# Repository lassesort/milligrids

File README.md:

# Milligrids
11hp version of Grids (topographic drum sequencer eurorack module) by Mutable Instruments

# NOTICE
IF YOU BUILD THIS DO NOT BOTHER OLIVIER GILLET, MUTABLE INSTRUMENTS or THE MUTABLE INSTRUMENTS FORUM WITH QUESTIONS! JUST DON'T! 

I might help you. But my priorities are in this order: my kids, my spouse, my job, my jobby, my mental health, looking out of the window, finishing my pile of synth related pcbs, watching videos on Youtube about country borders, manufacturing processes and cyclists from the 80s and 90s, and finally, somewhere close to the end of this list: helping you when you're failing at programming a Milligrids or needing help finding alternatives for parts in the BOM. ;)

# License
Code (AVR projects): GPL3.0.

Hardware: cc-by-sa-3.0

Grids: https://mutable-instruments.net/modules/grids/

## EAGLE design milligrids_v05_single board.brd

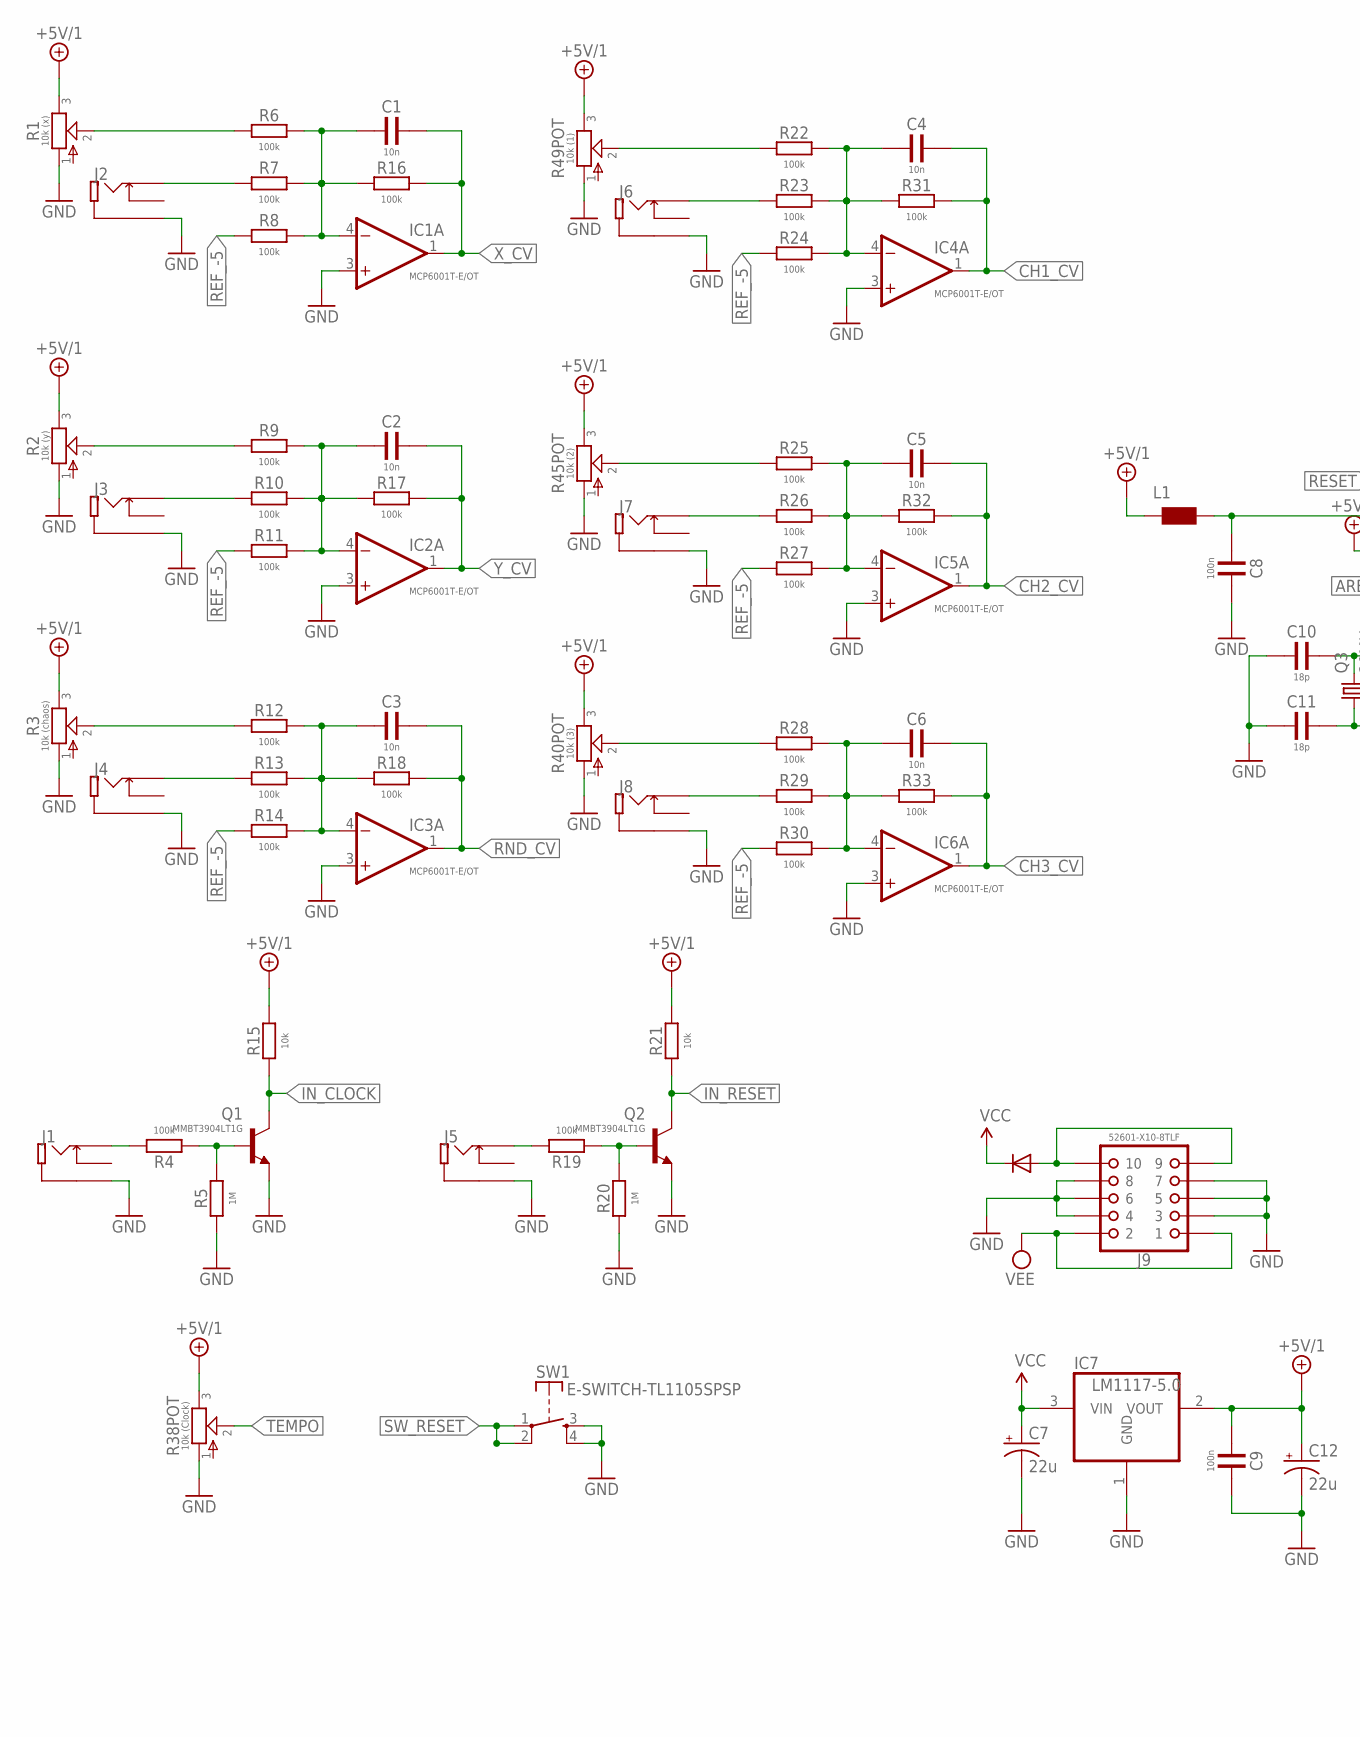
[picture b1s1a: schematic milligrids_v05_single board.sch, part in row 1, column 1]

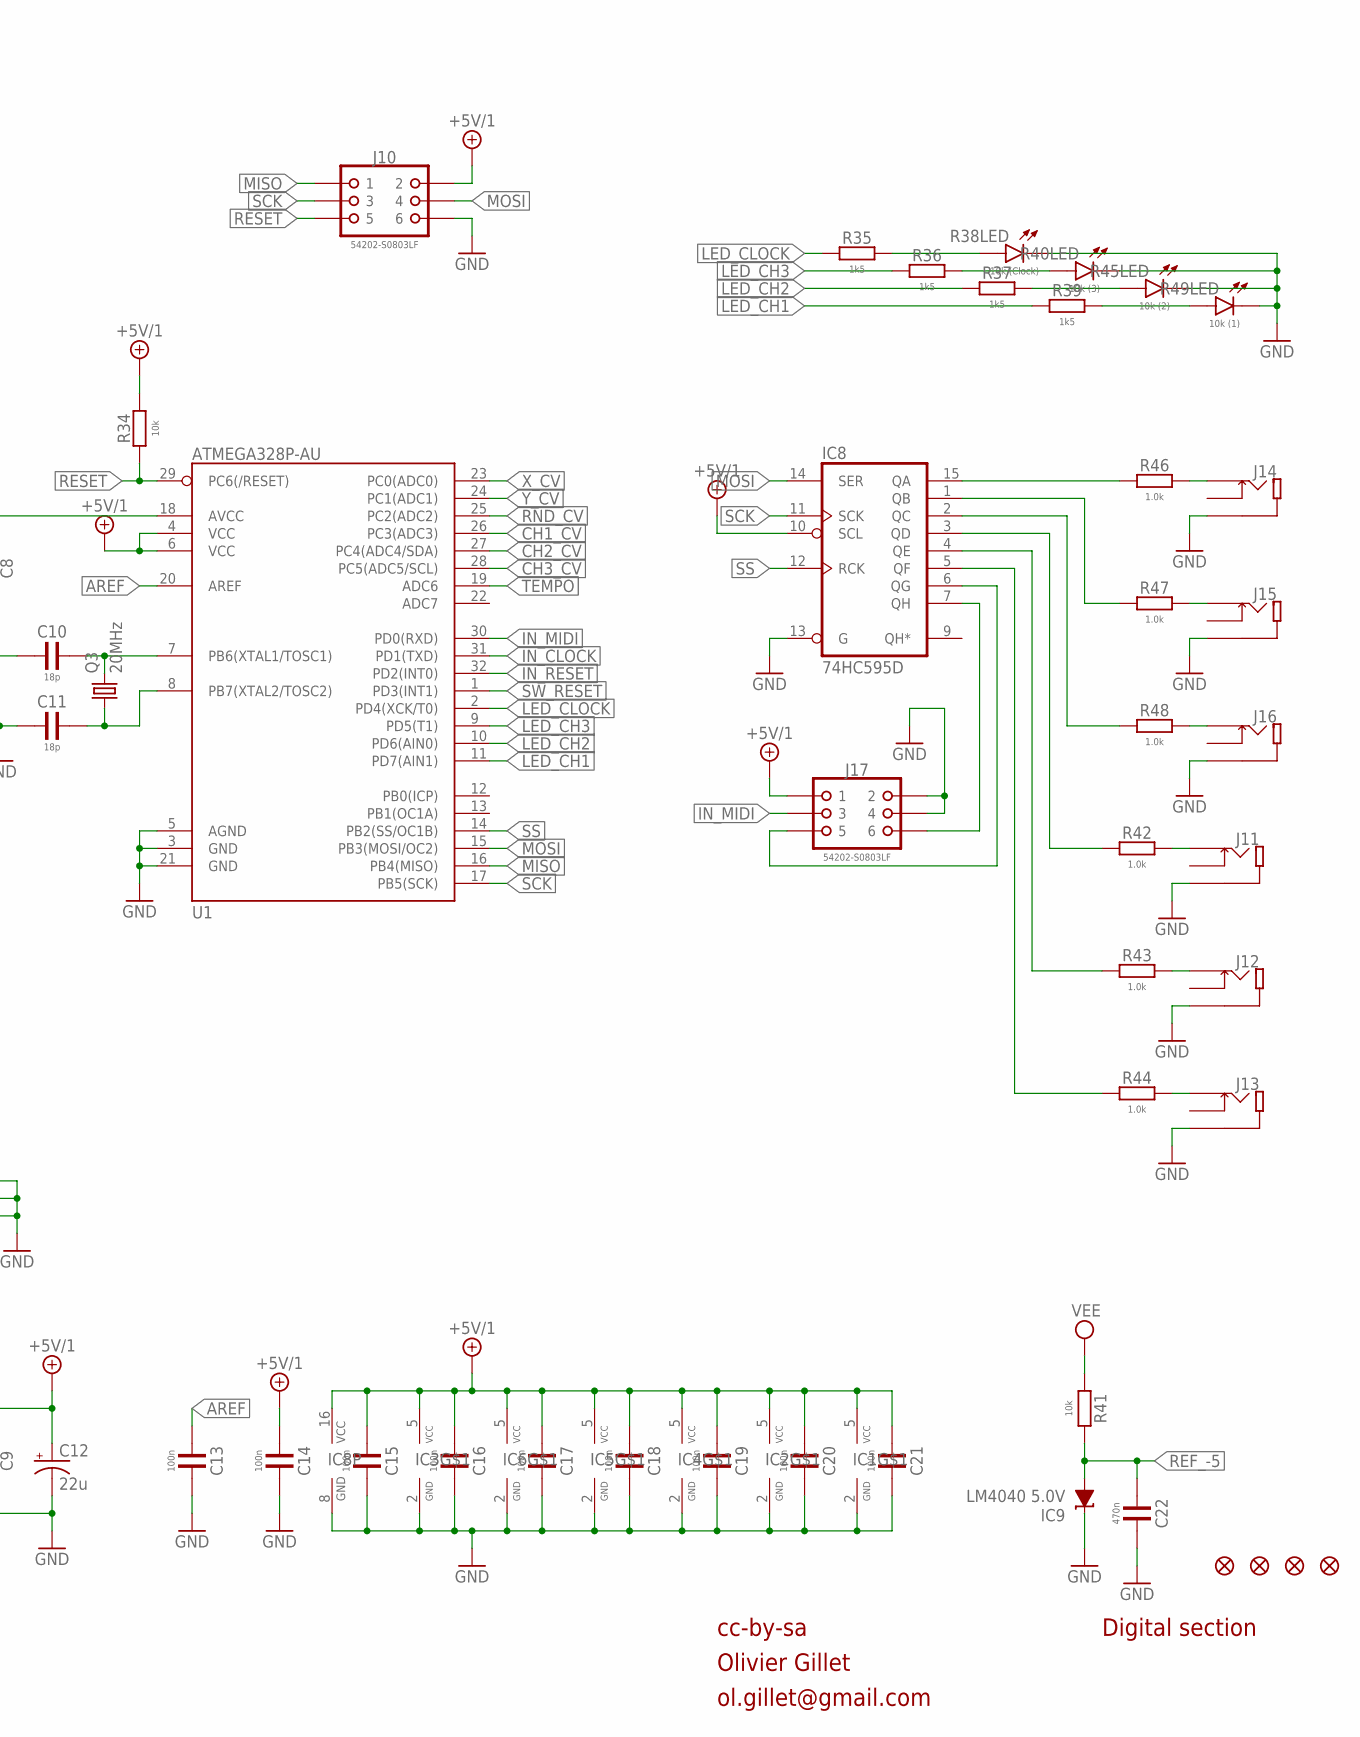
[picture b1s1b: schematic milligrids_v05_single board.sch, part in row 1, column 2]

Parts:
C1, C2, C3: 10n; C0805
C4, C5, C6: 10n; C0603
C7, C12: 22u; PANASONIC_C
C8, C9, C13, C14, C15, C16, C17, C18, C19, C20, C21: 100n; C0805
C10, C11: 18p; C0603
C22: 470n; C0805
D1: 1N5819HW; SOD123
IC1, IC2, IC3, IC4, IC5, IC6: MCP6001T-E/OT; SOT23-5
IC7: LM1117-5.0; SOT223
IC8: 74HC595D; SO16
IC9: LM4040 5.0V; DBZ_R-PDSO-G3
J1, J2, J3, J4, J5, J6, J7, J8, J11, J12, J13, J14, J15, J16: WQP-PJ301M6(THONKICONN)
J9: 52601-X10-8TLF; 52601-(X)10-8TLF
J10, J17: 54202-S0803LF
JP2, JP3, JP4, JP5: FIDUCIAL1X2; FIDUCIAL-1X2
L1: WE-CBF_0603; 0603
Q1, Q2: MMBT3904LT1G; SOT23-3
Q3: 20MHz; HC49UP
R1: 10k (x); SONGHUEI-RK0914
R2: 10k (y); SONGHUEI-RK0914
R3: 10k (chaos); SONGHUEI-RK0914
R4, R6, R7, R8, R9, R10, R11, R12, R13, R14, R16, R17, R18, R19, R22, R23, R24, R25, R26, R27, R28, R29, R30, R31, R32, R33: 100k; R0603
R5, R20: 1M; R0603
R15, R21, R34, R41: 10k; R0805
R35, R36, R37, R39: 1k5; R0805
R38: 10k (Clock); BOURNS-PTL30
R40: 10k (3); BOURNS-PTL30
R42, R43, R44, R46, R47, R48: 1.0k; R0805
R45: 10k (2); BOURNS-PTL30
R49: 10k (1); BOURNS-PTL30
SW1: E-SWITCH-TL1105SPSP; E-SWITCH-TL1105SP
U1: ATMEGA328P-AU; TQFP32-08

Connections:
+5V/1: C9.1, C12.+, C14.1, C15.1, C16.1, C17.1, C18.1, C19.1, C20.1, C21.1, IC1.5 (VCC), IC2.5 (VCC), IC3.5 (VCC), IC4.5 (VCC), IC5.5 (VCC), IC6.5 (VCC), IC7.2 (VOUT), IC8.10 (SCL), IC8.16 (VCC), J10.2, J17.1, L1.1, R1.3, R2.3, R3.3, R15.2, R21.2, R34.2, R38.3, R40.3, R45.3, R49.3, U1.4 (VCC), U1.6 (VCC)
AREF: C13.1, U1.20 (AREF)
CH1_ACC: J11.P3 (3), R42.2
CH1_CV: C4.2, IC4.1 (OUT), R31.2, U1.26 (PC3(ADC3))
CH1_JACK: J6.P3 (3), R23.1
CH1_LED: R39.2, R49.B (A)
CH1_POT: R22.1, R49.2
CH1_TRIG: J14.P3 (3), R46.2
CH2_ACC: J12.P3 (3), R43.2
CH2_CV: C5.2, IC5.1 (OUT), R32.2, U1.27 (PC4(ADC4/SDA))
CH2_JACK: J7.P3 (3), R26.1
CH2_LED: R37.2, R45.B (A)
CH2_POT: R25.1, R45.2
CH2_TRIG: J15.P3 (3), R47.2
CH3_ACC: J13.P3 (3), R44.2
CH3_CV: C6.2, IC6.1 (OUT), R33.2, U1.28 (PC5(ADC5/SCL))
CH3_JACK: J8.P3 (3), R29.1
CH3_LED: R36.2, R40.B (A)
CH3_TRIG: J16.P3 (3), R48.2
CH_POT: R28.1, R40.2
CLK_LED: R35.2, R38.B (A)
CLOCK_OUT: IC8.6 (QG), J17.5
GATE1_IN: J1.P3 (3), R4.2
GATE2_IN: J5.P3 (3), R19.2
GND: C7.-, C8.2, C9.2, C10.1, C11.1, C12.-, C13.2, C14.2, C15.2, C16.2, C17.2, C18.2, C19.2, C20.2, C21.2, C22.2, IC1.2 (GND), IC1.3 (+IN), IC2.2 (GND), IC2.3 (+IN), IC3.2 (GND), IC3.3 (+IN), IC4.2 (GND), IC4.3 (+IN), IC5.2 (GND), IC5.3 (+IN), IC6.2 (GND), IC6.3 (+IN), IC7.1 (GND), IC8.8 (GND), IC8.13 (G), IC9.1 (C), J1.P1 (1), J2.P1 (1), J3.P1 (1), J4.P1 (1), J5.P1 (1), J6.P1 (1), J7.P1 (1), J8.P1 (1), J9.3, J9.4, J9.5, J9.6, J9.7, J9.8, J10.6, J11.P1 (1), J12.P1 (1), J13.P1 (1), J14.P1 (1), J15.P1 (1), J16.P1 (1), J17.2, J17.4, Q1.2 (E), Q2.2 (E), R1.1, R2.1, R3.1, R5.1, R20.1, R38.1, R38.E (K), R40.1, R40.E (K), R45.1, R45.E (K), R49.1, R49.E (K), SW1.3, SW1.4, U1.3 (GND), U1.5 (AGND), U1.21 (GND)
IN_CLOCK: Q1.3 (C), R15.1, U1.31 (PD1(TXD))
IN_MIDI: J17.3, U1.30 (PD0(RXD))
IN_RESET: Q2.3 (C), R21.1, U1.32 (PD2(INT0))
LED_CH1: R39.1, U1.11 (PD7(AIN1))
LED_CH2: R37.1, U1.10 (PD6(AIN0))
LED_CH3: R36.1, U1.9 (PD5(T1))
LED_CLOCK: R35.1, U1.2 (PD4(XCK/T0))
MISO: J10.1, U1.16 (PB4(MISO))
MOSI: IC8.14 (SER), J10.4, U1.15 (PB3(MOSI/OC2))
unnamed: Q1.1 (B), R4.1, R5.2
unnamed: Q2.1 (B), R19.1, R20.2
unnamed: D1.A, J9.9, J9.10
unnamed: C2.1, IC2.4 (-IN), R9.2, R10.2, R11.2, R17.1
unnamed: C3.1, IC3.4 (-IN), R12.2, R13.2, R14.2, R18.1
unnamed: C4.1, IC4.4 (-IN), R22.2, R23.2, R24.2, R31.1
unnamed: C5.1, IC5.4 (-IN), R25.2, R26.2, R27.2, R32.1
unnamed: C6.1, IC6.4 (-IN), R28.2, R29.2, R30.2, R33.1
unnamed: IC8.15 (QA), R46.1
unnamed: IC8.1 (QB), R47.1
unnamed: C1.1, IC1.4 (-IN), R6.2, R7.2, R8.2, R16.1
unnamed: IC8.2 (QC), R48.1
unnamed: IC8.3 (QD), R42.1
unnamed: IC8.4 (QE), R43.1
unnamed: IC8.5 (QF), R44.1
unnamed: C8.1, L1.2, U1.18 (AVCC)
unnamed: C11.2, Q3.1, U1.8 (PB7(XTAL2/TOSC2))
unnamed: C10.2, Q3.2, U1.7 (PB6(XTAL1/TOSC1))
RANDOM_GATE: IC8.7 (QH), J17.6
REF_-5: C22.1, IC9.2 (A), R8.1, R11.1, R14.1, R24.1, R27.1, R30.1, R41.2
RESET: J10.5, R34.1, U1.29 (PC6(/RESET))
RND_CV: C3.2, IC3.1 (OUT), R18.2, U1.25 (PC2(ADC2))
RND_JACK: J4.P3 (3), R13.1
RND_POT: R3.2, R12.1
SCK: IC8.11 (SCK), J10.3, U1.17 (PB5(SCK))
SS: IC8.12 (RCK), U1.14 (PB2(SS/OC1B))
SW_RESET: SW1.1, SW1.2, U1.1 (PD3(INT1))
TEMPO: R38.2, U1.19 (ADC6)
VCC: C7.+, D1.C, IC7.3 (VIN)
VEE: J9.1, J9.2, R41.1
X_CV: C1.2, IC1.1 (OUT), R16.2, U1.23 (PC0(ADC0))
X_JACK: J2.P3 (3), R7.1
X_POT: R1.2, R6.1
Y_CV: C2.2, IC2.1 (OUT), R17.2, U1.24 (PC1(ADC1))
Y_JACK: J3.P3 (3), R10.1
Y_POT: R2.2, R9.1

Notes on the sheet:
cc-by-sa
Olivier Gillet
ol.gillet@gmail.com
Digital section

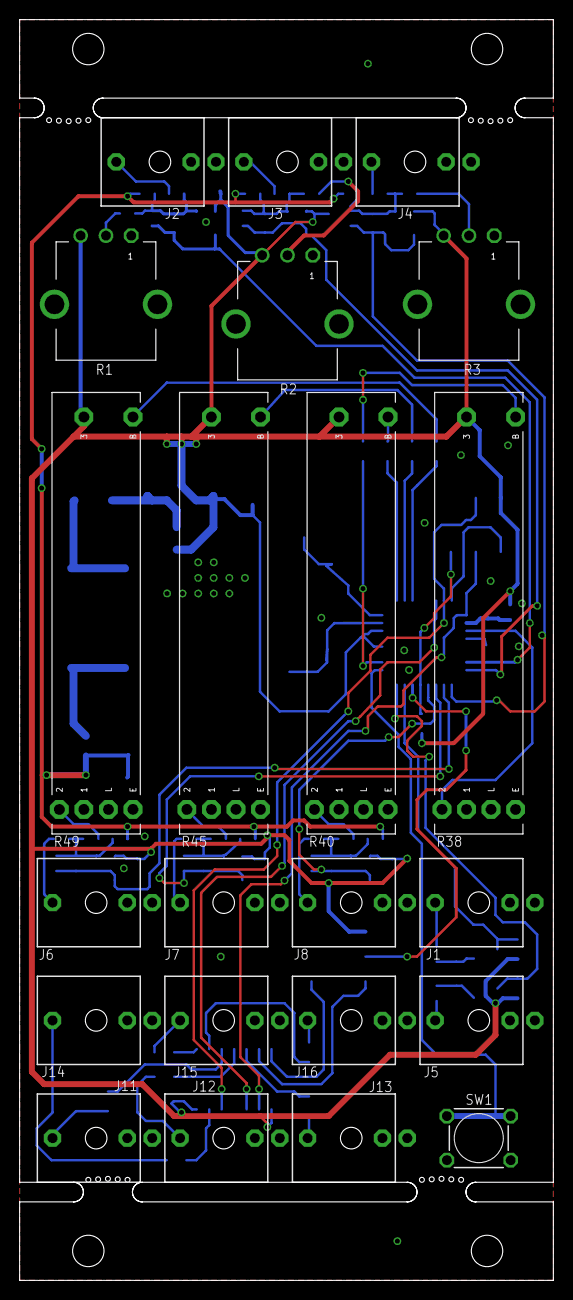
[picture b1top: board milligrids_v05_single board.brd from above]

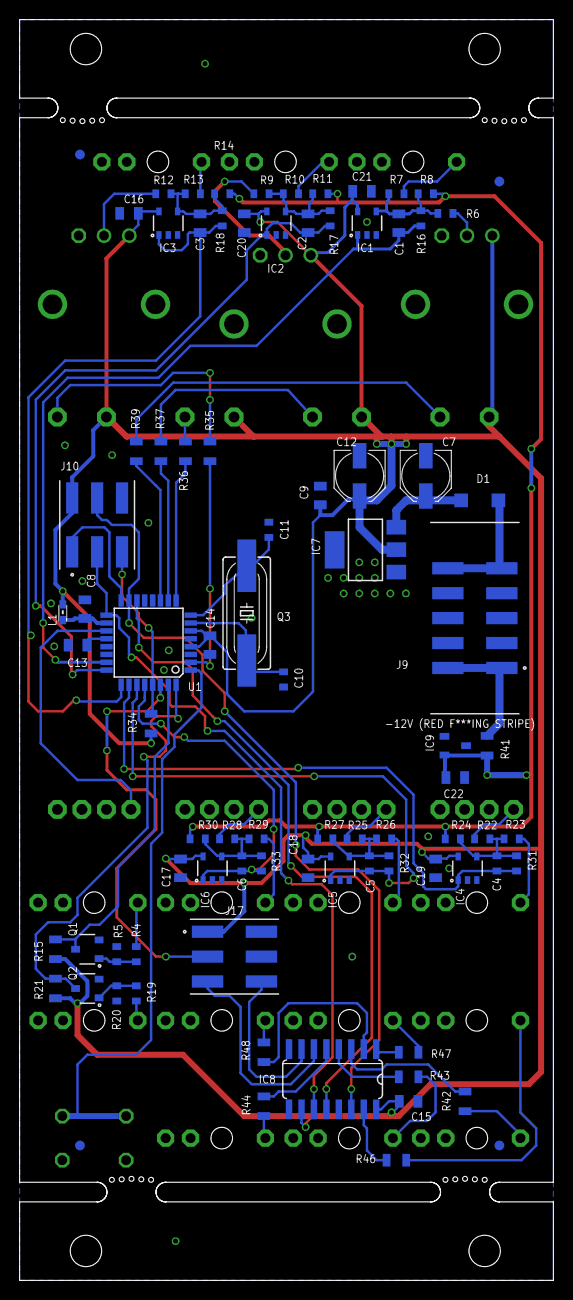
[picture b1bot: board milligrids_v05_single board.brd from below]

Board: 2 copper layers, 54.4 x 128.5 mm, 108 parts (86 on the bottom side), 70 nets.

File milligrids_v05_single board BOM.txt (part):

Partlist exported from C:/Users/Lasse/Documents/eagle/DIY FUN/DIY Grids/milligrids_v05_single board.sch at 20-11-2018 23:39:35

Part Value                   Device                  Package                 Description                                       
C1   10n                     C0805                   C0805                   Capacitor 0805 Package                            
C2   10n                     C0805                   C0805                   Capacitor 0805 Package                            
C3   10n                     C0805                   C0805                   Capacitor 0805 Package                            
C4   10n                     C0603                   C0603                   Capacitor 0603 Package                            
C5   10n                     C0603                   C0603                   Capacitor 0603 Package                            
C6   10n                     C0603                   C0603                   Capacitor 0603 Package 
  For C4, C5, C6 0805 package is OK

C7   22u                     CPOL-USC                PANASONIC_C             POLARIZED CAPACITOR, American symbol              
C8   100n                    C0805                   C0805                   Capacitor 0805 Package                            
C9   100n                    C0805                   C0805                   Capacitor 0805 Package                            
C10  18p                     C0603                   C0603                   Capacitor 0603 Package                            
C11  18p                     C0603                   C0603                   Capacitor 0603 Package                            
C12  22u                     CPOL-USC                PANASONIC_C             POLARIZED CAPACITOR, American symbol              
C13  100n                    C0805                   C0805                   Capacitor 0805 Package                            
C14  100n                    C0805                   C0805                   Capacitor 0805 Package                            
C15  100n                    C0805                   C0805                   Capacitor 0805 Package                            
C16  100n                    C0805                   C0805                   Capacitor 0805 Package                            
C17  100n                    C0805                   C0805                   Capacitor 0805 Package                            
C18  100n                    C0805                   C0805                   Capacitor 0805 Package                            
C19  100n                    C0805                   C0805                   Capacitor 0805 Package                            
C20  100n                    C0805                   C0805                   Capacitor 0805 Package                            
C21  100n                    C0805                   C0805                   Capacitor 0805 Package                            
C22  470n                    C0805                   C0805                   Capacitor 0805 Package                            
D1   1N5819HW                DIODE-SOD123            SOD123                  DIODE                                             
IC1  MCP6001T-E/OT           MCP6001T-E/OT           SOT23-5                                                                   
IC2  MCP6001T-E/OT           MCP6001T-E/OT           SOT23-5                                                                   
IC3  MCP6001T-E/OT           MCP6001T-E/OT           SOT23-5                                                                   
IC4  MCP6001T-E/OT           MCP6001T-E/OT           SOT23-5                                                                   
IC5  MCP6001T-E/OT           MCP6001T-E/OT           SOT23-5                                                                   
IC6  MCP6001T-E/OT           MCP6001T-E/OT           SOT23-5                                                                   
IC7  LM1117-5.0              REG1117                 SOT223                  800mA and 1A Low Dropout (LDO) Positive Regulator 
IC8  74HC595D                74HC595D                SO16                    8-bit SHIFT REGISTER, output latch                
IC9  LM4040 5.0V             LM4041C12DBZ            DBZ_R-PDSO-G3           PRECISION MICROPOWER SHUNT VOLTAGE REFERENCE      
J1   WQP-PJ301M6(THONKICONN) WQP-PJ301M6(THONKICONN) WQP-PJ301M6(THONKICONN)                                                   
J2   WQP-PJ301M6(THONKICONN) WQP-PJ301M6(THONKICONN) WQP-PJ301M6(THONKICONN)                                                   
J3   WQP-PJ301M6(THONKICONN) WQP-PJ301M6(THONKICONN) WQP-PJ301M6(THONKICONN)                                                   
J4   WQP-PJ301M6(THONKICONN) WQP-PJ301M6(THONKICONN) WQP-PJ301M6(THONKICONN)                                                   
J5   WQP-PJ301M6(THONKICONN) WQP-PJ301M6(THONKICONN) WQP-PJ301M6(THONKICONN)                                                   
J6   WQP-PJ301M6(THONKICONN) WQP-PJ301M6(THONKICONN) WQP-PJ301M6(THONKICONN)                                                   
J7   WQP-PJ301M6(THONKICONN) WQP-PJ301M6(THONKICONN) WQP-PJ301M6(THONKICONN)                                                   
J8   WQP-PJ301M6(THONKICONN) WQP-PJ301M6(THONKICONN) WQP-PJ301M6(THONKICONN)                                                   
J9   52601-X10-8TLF          52601-X10-8TLF          52601-(X)10-8TLF                                                          
J10  54202-S0803LF           54202-S0803LF           54202-S0803LF                                                             
J11  WQP-PJ301M6(THONKICONN) WQP-PJ301M6(THONKICONN) WQP-PJ301M6(THONKICONN)                                                   
J12  WQP-PJ301M6(THONKICONN) WQP-PJ301M6(THONKICONN) WQP-PJ301M6(THONKICONN)                                                   
J13  WQP-PJ301M6(THONKICONN) WQP-PJ301M6(THONKICONN) WQP-PJ301M6(THONKICONN)                                                   
J14  WQP-PJ301M6(THONKICONN) WQP-PJ301M6(THONKICONN) WQP-PJ301M6(THONKICONN)                                                   
J15  WQP-PJ301M6(THONKICONN) WQP-PJ301M6(THONKICONN) WQP-PJ301M6(THONKICONN)                                                   
J16  WQP-PJ301M6(THONKICONN) WQP-PJ301M6(THONKICONN) WQP-PJ301M6(THONKICONN)                                                   
J17  54202-S0803LF           54202-S0803LF           54202-S0803LF                                                             
JP2  FIDUCIAL1X2             FIDUCIAL1X2             FIDUCIAL-1X2            Fiducial Alignment Points                         
JP3  FIDUCIAL1X2             FIDUCIAL1X2             FIDUCIAL-1X2            Fiducial Alignment Points                         
JP4  FIDUCIAL1X2             FIDUCIAL1X2             FIDUCIAL-1X2            Fiducial Alignment Points                         
JP5  FIDUCIAL1X2             FIDUCIAL1X2             FIDUCIAL-1X2            Fiducial Alignment Points                         
L1                           WE-CBF_0603             0603                    SMD EMI Suppression Ferrite Beads                 
Q1   MMBT3904LT1G            MMBT3904LT1G            SOT23-3                                                                   
Q2   MMBT3904LT1G            MMBT3904LT1G            SOT23-3                                                                   
Q3   20MHz                   CRYSTALHC49UP           HC49UP                  CRYSTAL                                           
R1   10k (x)                 SONGHUEI-RK0914         SONGHUEI-RK0914         SONG HUEI RK0914 9mm POTENTIOMETER                
R2   10k (y)                 SONGHUEI-RK0914         SONGHUEI-RK0914         SONG HUEI RK0914 9mm POTENTIOMETER                
R3   10k (chaos)             SONGHUEI-RK0914         SONGHUEI-RK0914         SONG HUEI RK0914 9mm POTENTIOMETER                
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
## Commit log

2018-11-20 Rename milligrids_v05_single board.txt to milligrids_v05_single board BOM.txt
